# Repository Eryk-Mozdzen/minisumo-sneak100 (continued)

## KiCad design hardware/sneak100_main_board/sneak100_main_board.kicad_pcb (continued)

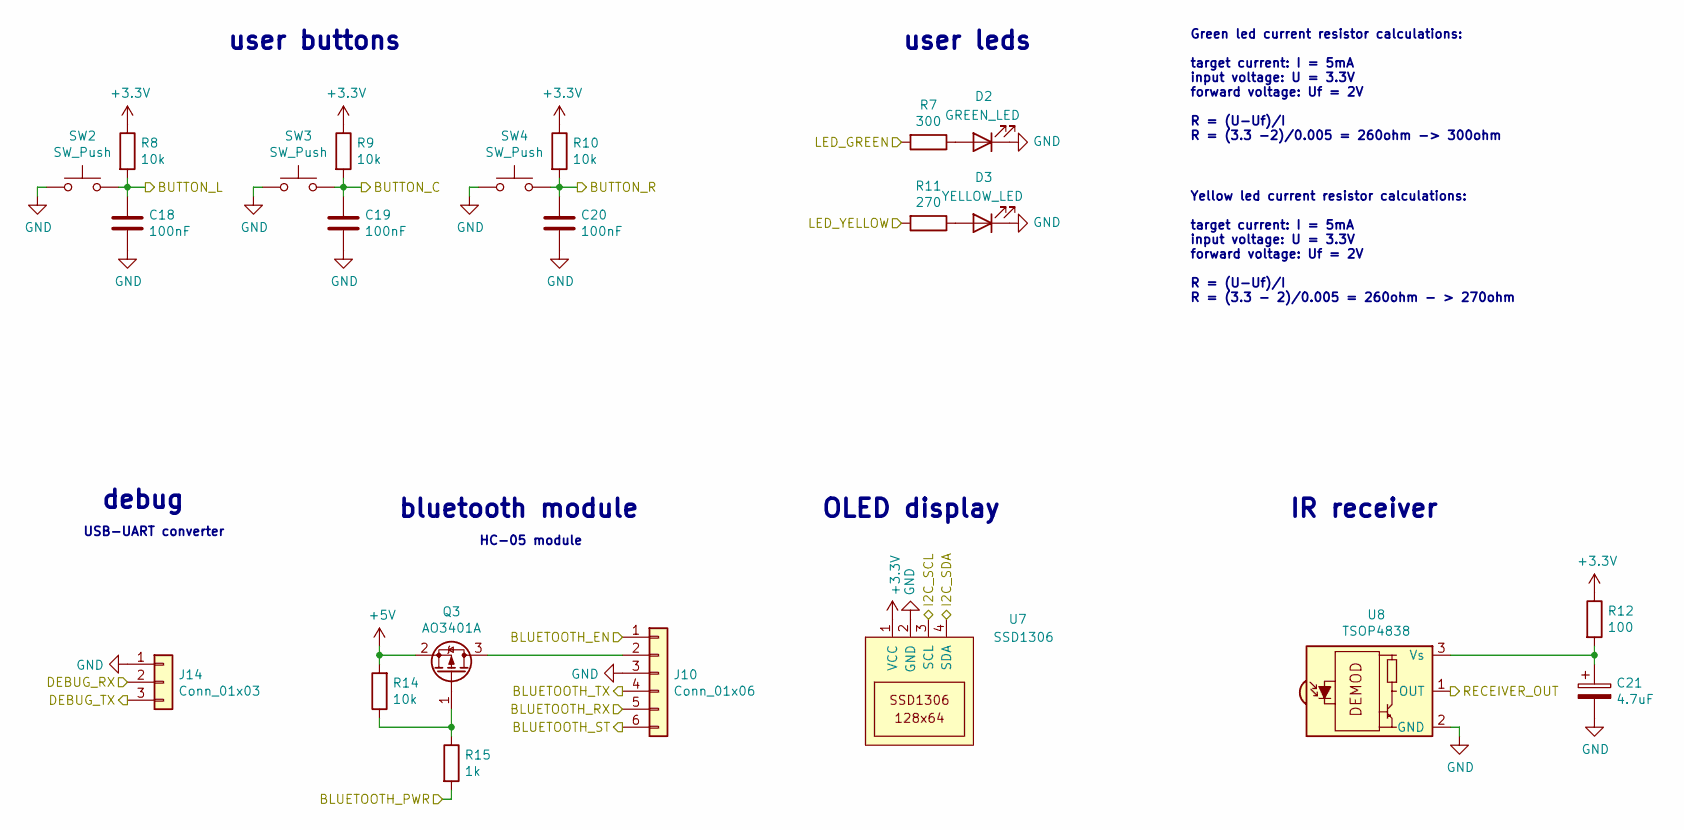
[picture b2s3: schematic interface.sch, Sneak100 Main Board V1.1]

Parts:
C18, C19, C20: 100nF; C_0603_1608Metric
C21: 4.7uF; CP_EIA-3216-18_Kemet-A
D2: GREEN_LED; LED_0603_1608Metric
D3: YELLOW_LED; LED_0603_1608Metric
J10: Conn_01x06; PinSocket_1x06_P2.54mm_Vertical
J14: Conn_01x03; PinSocket_1x03_P2.54mm_Vertical
Q3: AO3401A; SOT-23
R7: 300; R_0603_1608Metric
R8, R9, R10, R14: 10k; R_0603_1608Metric
R11: 270; R_0603_1608Metric
R12: 100; R_0603_1608Metric
R15: 1k; R_0603_1608Metric
SW2, SW3, SW4: SW_Push; SW_Push_1P1T_NO_6x6mm_H9.5mm
U7: SSD1306; SSD1306_module_screw
U8: TSOP4838; PinHeader_1x03_P2.54mm_Vertical

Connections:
+3V3: R8.1, R9.1, R10.1, R12.1, U7.1 (VCC); also elsewhere on the board
+5V: Q3.2 (S), R14.2; also elsewhere on the board
/controller/BLUETOOTH_EN: J10.1; also elsewhere on the board
/controller/BLUETOOTH_PWR: R15.2; also elsewhere on the board
/controller/BLUETOOTH_ST: J10.6; also elsewhere on the board
/controller/I2C1_SCL: U7.3 (SCL); also elsewhere on the board
/controller/I2C1_SDA: U7.4 (SDA); also elsewhere on the board
/controller/RECEIVER_OUT: U8.1 (OUT); also elsewhere on the board
/interface/BLUETOOTH_RX: J10.5; also elsewhere on the board
/interface/BLUETOOTH_TX: J10.4; also elsewhere on the board
/interface/BUTTON_C: C19.1, R9.2, SW3.2; also elsewhere on the board
/interface/BUTTON_L: C18.1, R8.2, SW2.2; also elsewhere on the board
/interface/BUTTON_R: C20.1, R10.2, SW4.2; also elsewhere on the board
/interface/DEBUG_RX: J14.2; also elsewhere on the board
/interface/DEBUG_TX: J14.3; also elsewhere on the board
/interface/LED_GREEN: R7.2; also elsewhere on the board
/interface/LED_YELLOW: R11.2; also elsewhere on the board
GND: C18.2, C19.2, C20.2, C21.2, D2.1 (K), D3.1 (K), J10.3, J14.1, SW2.1, SW3.1, SW4.1, U7.2 (GND), U8.2 (GND); also elsewhere on the board
unnamed: C21.1, R12.2, U8.3 (Vs)
unnamed: D2.2 (A), R7.1
unnamed: D3.2 (A), R11.1
unnamed: J10.2, Q3.3 (D)
unnamed: Q3.1 (G), R14.1, R15.1

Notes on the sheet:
Green led current resistor calculations: target current: I = 5mA input voltage: U = 3.3V forward voltage: Uf = 2V R = (U-Uf)/I R = (3.3 -2)/0.005 = 260ohm -> 300ohm
user buttons
user leds
bluetooth module
OLED display
IR receiver
Yellow led current resistor calculations: target current: I = 5mA input voltage: U = 3.3V forward voltage: Uf = 2V R = (U-Uf)/I R = (3.3 - 2)/0.005 = 260ohm - > 270ohm
HC-05 module
debug
USB-UART converter

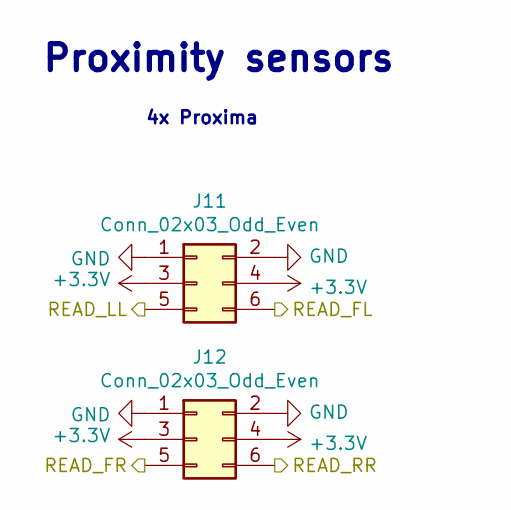
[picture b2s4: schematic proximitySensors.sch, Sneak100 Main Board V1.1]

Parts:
J11, J12: Conn_02x03_Odd_Even; PinSocket_2x03_P2.54mm_Horizontal

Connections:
+3V3: J11.3, J11.4, J12.3, J12.4; also elsewhere on the board
/controller/PROXIMITY_FL: J11.6; also elsewhere on the board
/controller/PROXIMITY_FR: J12.5; also elsewhere on the board
/controller/PROXIMITY_LL: J11.5; also elsewhere on the board
/controller/PROXIMITY_RR: J12.6; also elsewhere on the board
GND: J11.1, J11.2, J12.1, J12.2; also elsewhere on the board

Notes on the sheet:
Proximity sensors
4x Proxima

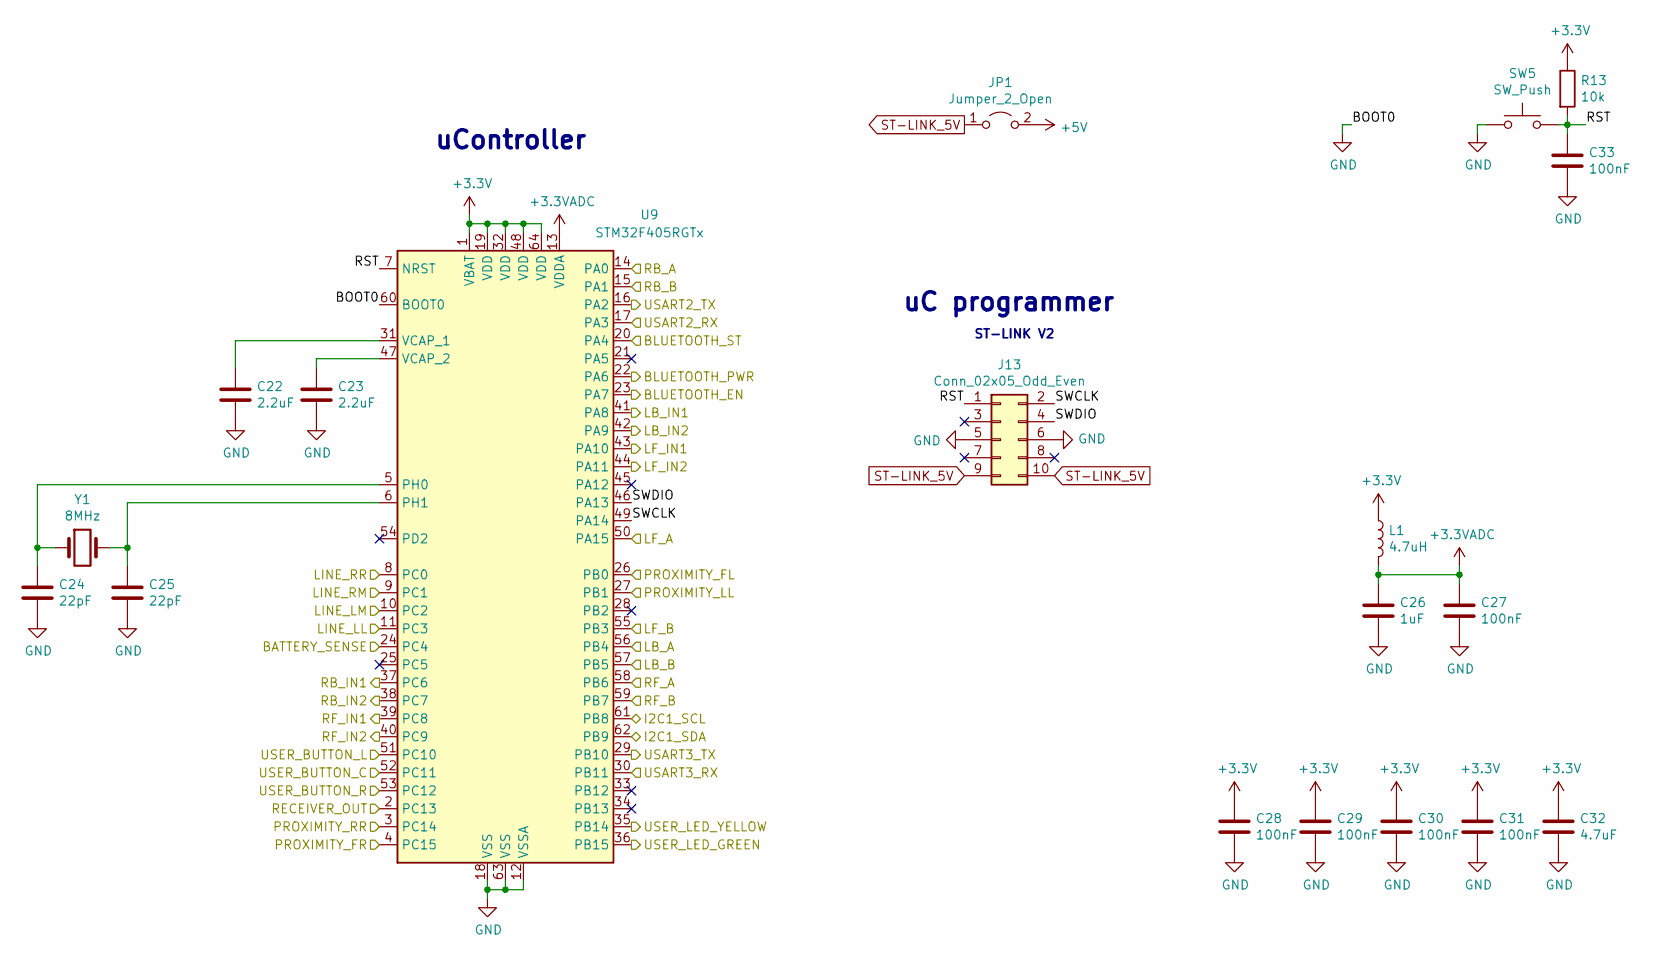
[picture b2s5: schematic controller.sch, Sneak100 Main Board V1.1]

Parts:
C22, C23: 2.2uF; C_0603_1608Metric
C24, C25: 22pF; C_0603_1608Metric
C26: 1uF; C_0603_1608Metric
C27, C28, C29, C30, C31, C33: 100nF; C_0603_1608Metric
C32: 4.7uF; C_0603_1608Metric
J13: Conn_02x05_Odd_Even; IDC-Header_2x05_P2.54mm_Vertical
JP1: Jumper_2_Open; PinHeader_1x03_P2.54mm_Vertical
L1: 4.7uH; L_0805_2012Metric
R13: 10k; R_0603_1608Metric
SW5: SW_Push; SW_Push_1P1T_NO_6x6mm_H9.5mm
U9: STM32F405RGTx; LQFP-64_10x10mm_P0.5mm
Y1: 8MHz; Crystal_SMD_5032-2Pin_5.0x3.2mm

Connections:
+3.3VADC: C26.1, C27.1, L1.2, U9.13 (VDDA)
+3V3: C28.1, C29.1, C30.1, C31.1, C32.1, L1.1, R13.1, U9.1 (VBAT), U9.19 (VDD), U9.32 (VDD), U9.48 (VDD), U9.64 (VDD); also elsewhere on the board
+5V: JP1.2 (B); also elsewhere on the board
/controller/BATTERY_SENSE: U9.24 (PC4); also elsewhere on the board
/controller/BLUETOOTH_EN: U9.23 (PA7); also elsewhere on the board
/controller/BLUETOOTH_PWR: U9.22 (PA6); also elsewhere on the board
/controller/BLUETOOTH_ST: U9.20 (PA4); also elsewhere on the board
/controller/I2C1_SCL: U9.61 (PB8); also elsewhere on the board
/controller/I2C1_SDA: U9.62 (PB9); also elsewhere on the board
/controller/LB_A: U9.56 (PB4); also elsewhere on the board
/controller/LB_B: U9.57 (PB5); also elsewhere on the board
/controller/LB_IN1: U9.41 (PA8); also elsewhere on the board
/controller/LB_IN2: U9.42 (PA9); also elsewhere on the board
/controller/LF_A: U9.50 (PA15); also elsewhere on the board
/controller/LF_B: U9.55 (PB3); also elsewhere on the board
/controller/LF_IN1: U9.43 (PA10); also elsewhere on the board
/controller/LF_IN2: U9.44 (PA11); also elsewhere on the board
/controller/LINE_LL: U9.11 (PC3); also elsewhere on the board
/controller/LINE_LM: U9.10 (PC2); also elsewhere on the board
/controller/LINE_RM: U9.9 (PC1); also elsewhere on the board
/controller/LINE_RR: U9.8 (PC0); also elsewhere on the board
/controller/PROXIMITY_FL: U9.26 (PB0); also elsewhere on the board
/controller/PROXIMITY_FR: U9.4 (PC15); also elsewhere on the board
/controller/PROXIMITY_LL: U9.27 (PB1); also elsewhere on the board
/controller/PROXIMITY_RR: U9.3 (PC14); also elsewhere on the board
/controller/RB_A: U9.14 (PA0); also elsewhere on the board
/controller/RB_B: U9.15 (PA1); also elsewhere on the board
/controller/RB_IN1: U9.37 (PC6); also elsewhere on the board
/controller/RB_IN2: U9.38 (PC7); also elsewhere on the board
/controller/RECEIVER_OUT: U9.2 (PC13); also elsewhere on the board
/controller/RF_A: U9.58 (PB6); also elsewhere on the board
/controller/RF_B: U9.59 (PB7); also elsewhere on the board
/controller/RF_IN1: U9.39 (PC8); also elsewhere on the board
/controller/RF_IN2: U9.40 (PC9); also elsewhere on the board
/controller/RST: C33.1, J13.1, R13.2, SW5.2, U9.7 (NRST)
/controller/SWCLK: J13.2, U9.49 (PA14)
/controller/SWDIO: J13.4, U9.46 (PA13)
/interface/BLUETOOTH_RX: U9.16 (PA2); also elsewhere on the board
/interface/BLUETOOTH_TX: U9.17 (PA3); also elsewhere on the board
/interface/BUTTON_C: U9.52 (PC11); also elsewhere on the board
/interface/BUTTON_L: U9.51 (PC10); also elsewhere on the board
/interface/BUTTON_R: U9.53 (PC12); also elsewhere on the board
/interface/DEBUG_RX: U9.30 (PB11); also elsewhere on the board
/interface/DEBUG_TX: U9.29 (PB10); also elsewhere on the board
/interface/LED_GREEN: U9.36 (PB15); also elsewhere on the board
/interface/LED_YELLOW: U9.35 (PB14); also elsewhere on the board
GND: C22.2, C23.2, C24.2, C25.2, C26.2, C27.2, C28.2, C29.2, C30.2, C31.2, C32.2, C33.2, J13.5, J13.6, SW5.1, U9.12 (VSSA), U9.18 (VSS), U9.60 (BOOT0), U9.63 (VSS); also elsewhere on the board
unnamed: C22.1, U9.31 (VCAP_1)
unnamed: C23.1, U9.47 (VCAP_2)
unnamed: C24.1, U9.5 (PH0), Y1.1
unnamed: C25.1, U9.6 (PH1), Y1.2
ST-LINK_5V: J13.9, J13.10, JP1.1 (A)

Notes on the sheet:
uController
uC programmer
ST-LINK V2

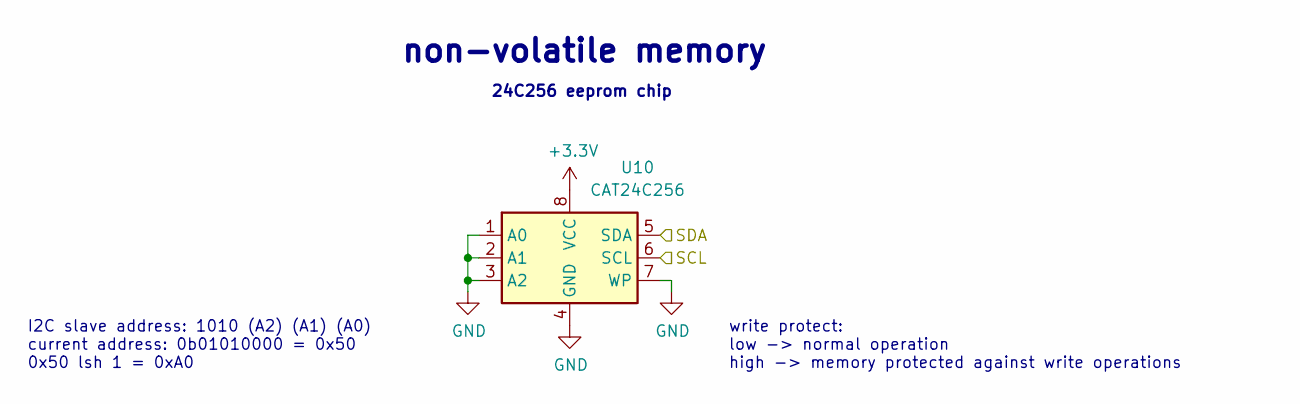
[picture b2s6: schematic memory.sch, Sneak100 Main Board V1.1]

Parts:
U10: CAT24C256; SOIC-8_3.9x4.9mm_P1.27mm

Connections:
+3V3: U10.8 (VCC); also elsewhere on the board
/controller/I2C1_SCL: U10.6 (SCL); also elsewhere on the board
/controller/I2C1_SDA: U10.5 (SDA); also elsewhere on the board
GND: U10.1 (A0), U10.2 (A1), U10.3 (A2), U10.4 (GND), U10.7 (WP); also elsewhere on the board

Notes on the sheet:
I2C slave address: 1010 (A2) (A1) (A0) current address: 0b01010000 = 0x50 0x50 lsh 1 = 0xA0
write protect: low -> normal operation high -> memory protected against write operations
non-volatile memory
24C256 eeprom chip

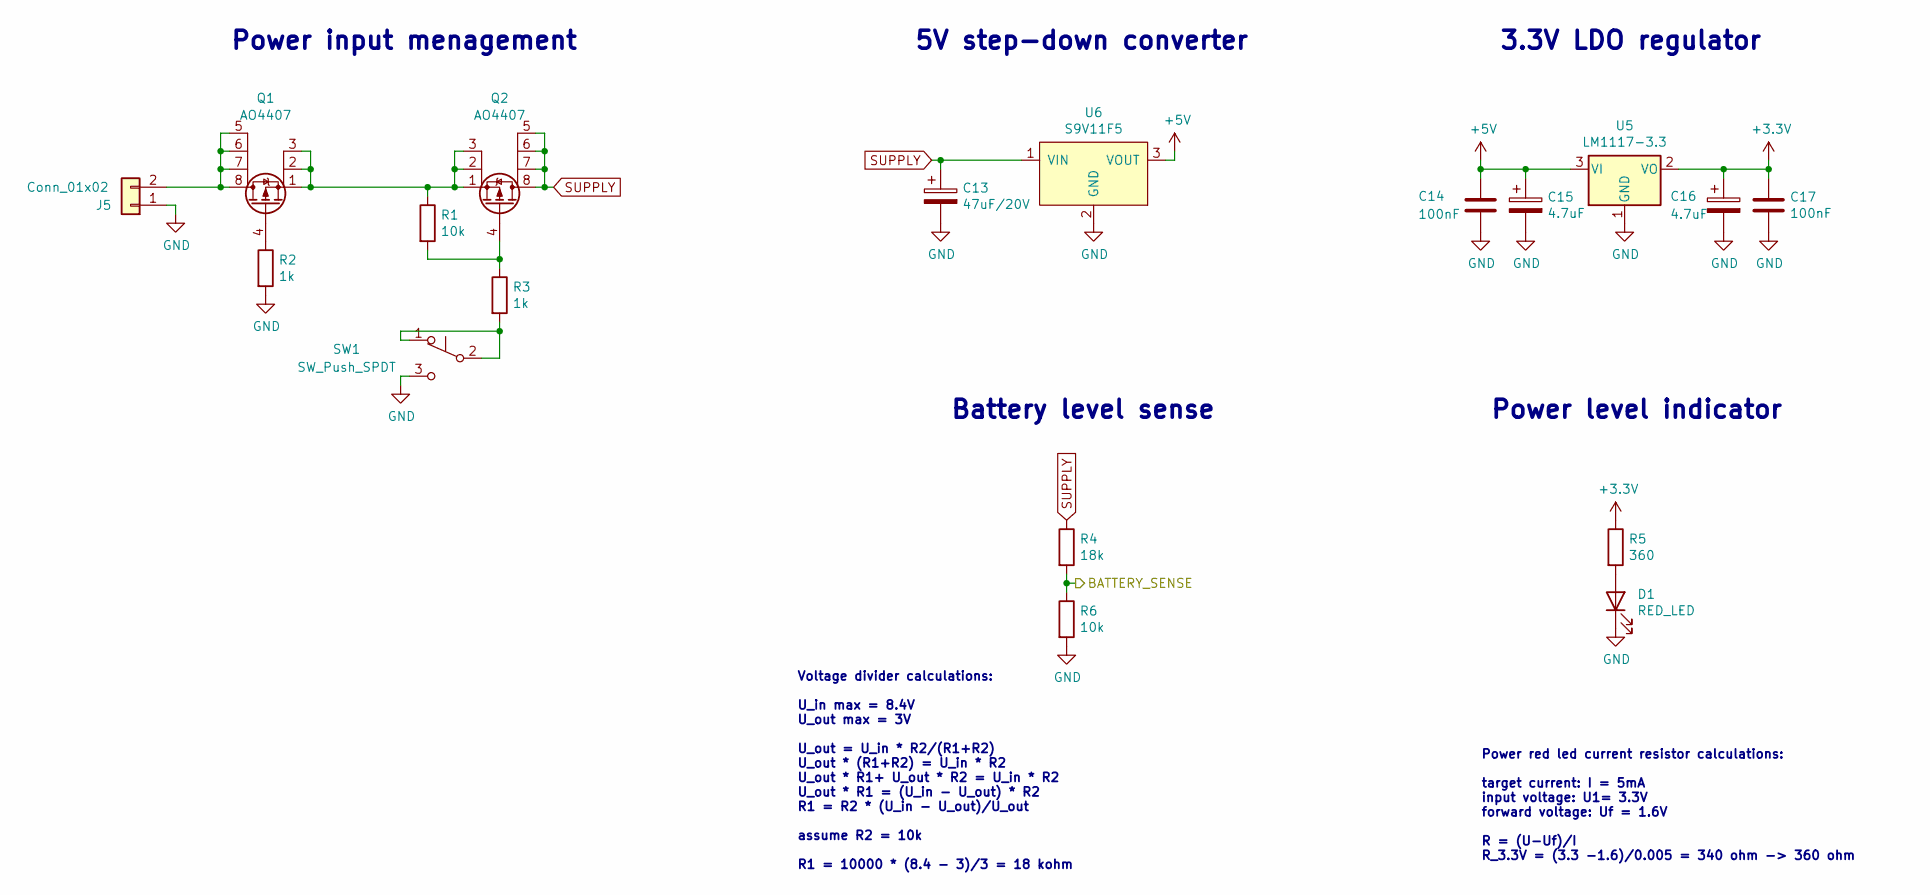
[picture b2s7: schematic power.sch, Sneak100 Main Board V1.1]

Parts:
C13: 47uF/20V; CP_EIA-7343-31_Kemet-D
C14, C17: 100nF; C_0603_1608Metric
C15, C16: 4.7uF; CP_EIA-3216-18_Kemet-A
D1: RED_LED; LED_0603_1608Metric
J5: Conn_01x02; PinHeader_1x02_P2.54mm_Horizontal
Q1, Q2: AO4407; SOIC-8_3.9x4.9mm_P1.27mm
R1, R6: 10k; R_0603_1608Metric
R2, R3: 1k; R_0603_1608Metric
R4: 18k; R_0603_1608Metric
R5: 360; R_0603_1608Metric
SW1: SW_Push_SPDT; ESP2010_90
U5: LM1117-3.3; SOT-223-3_TabPin2
U6: S9V11F5; S9V11F5_module

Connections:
+3V3: C16.1, C17.1, R5.1, U5.2 (VO); also elsewhere on the board
+5V: C14.1, C15.1, U5.3 (VI), U6.3 (VOUT); also elsewhere on the board
/controller/BATTERY_SENSE: R4.2, R6.1; also elsewhere on the board
GND: C13.2, C14.2, C15.2, C16.2, C17.2, D1.1 (K), J5.1, R2.2, R6.2, SW1.3 (C), U5.1 (GND), U6.2 (GND); also elsewhere on the board
unnamed: D1.2 (A), R5.2
unnamed: J5.2, Q1.5, Q1.6, Q1.7, Q1.8
unnamed: Q1.1, Q1.2, Q1.3, Q2.1, Q2.2, Q2.3, R1.1
unnamed: Q1.4, R2.1
unnamed: Q2.4, R1.2, R3.1
unnamed: R3.2, SW1.1 (A), SW1.2 (B)
SUPPLY: C13.1, Q2.5, Q2.6, Q2.7, Q2.8, R4.1, U6.1 (VIN); also elsewhere on the board

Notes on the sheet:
5V step-down converter
Battery level sense
Power level indicator
Power input menagement
3.3V LDO regulator
Voltage divider calculations: U_in max = 8.4V U_out max = 3V U_out = U_in * R2/(R1+R2) U_out * (R1+R2) = U_in * R2 U_out * R1+ U_out * R2 = U_in * R2 U_out * R1 = (U_in - U_out) * R2 R1 = R2 * (U_in - U_out)/U_out assume R2 = 10k R1 = 10000 * (8.4 - 3)/3 = 18 kohm
Power red led current resistor calculations: target current: I = 5mA input voltage: U1= 3.3V forward voltage: Uf = 1.6V R = (U-Uf)/I R_3.3V = (3.3 -1.6)/0.005 = 340 ohm -> 360 ohm

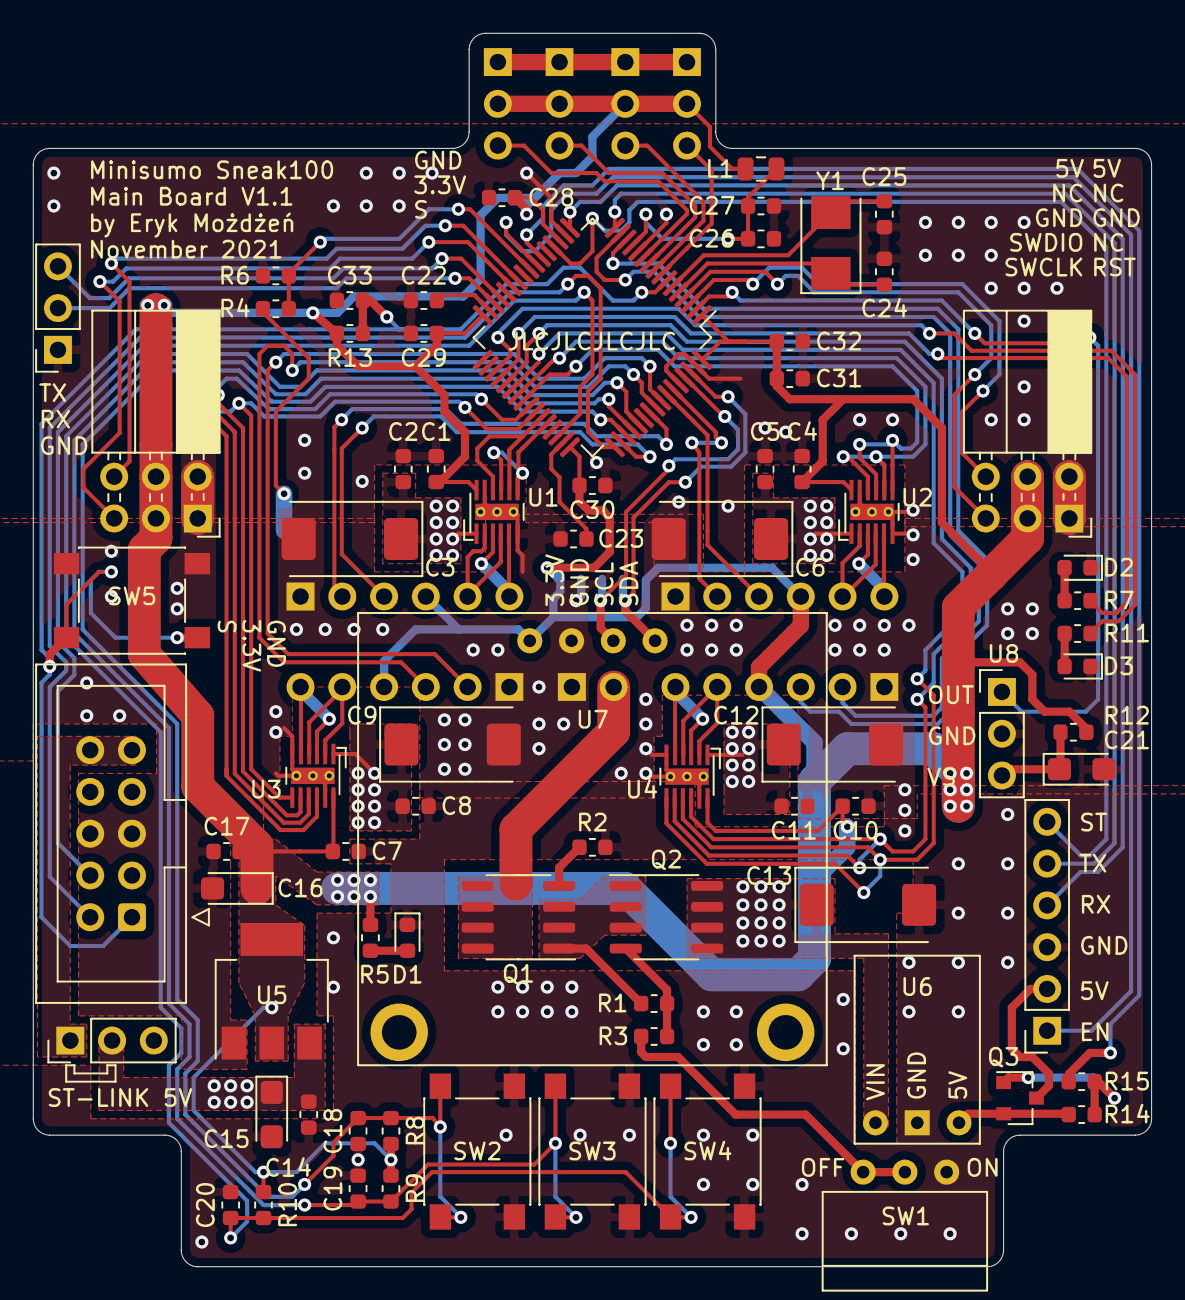
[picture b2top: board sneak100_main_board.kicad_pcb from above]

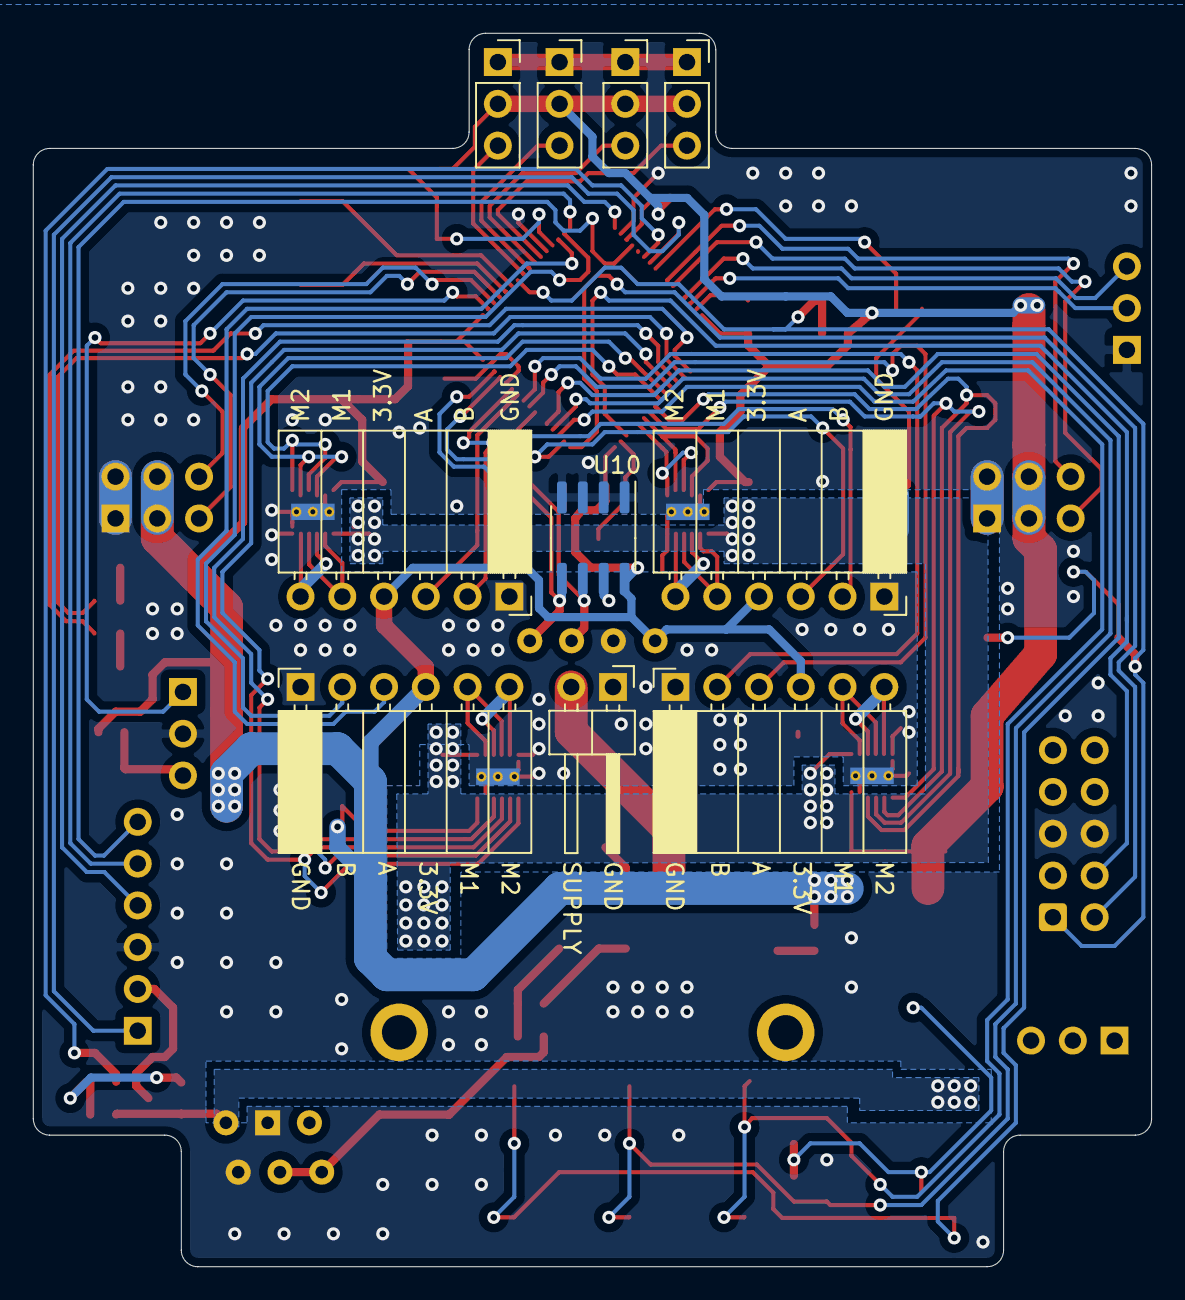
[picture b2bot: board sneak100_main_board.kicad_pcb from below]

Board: 2 copper layers, 68.0 x 75.0 mm, 86 parts (10 on the bottom side), 72 nets.

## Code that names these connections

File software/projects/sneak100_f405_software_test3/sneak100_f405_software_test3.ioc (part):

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Mcu.Name=STM32F405RGTx
Mcu.Package=LQFP64
Mcu.UserName=STM32F405RGTx
PA0-WKUP.GPIOParameters=GPIO_Label
PA0-WKUP.GPIO_Label=MOT1_IN1
PA0-WKUP.Signal=S_TIM5_CH1
PA1.GPIOParameters=GPIO_Label
PA1.GPIO_Label=MOT1_IN2
PA1.Signal=S_TIM5_CH2
PA11.GPIOParameters=GPIO_Label
PA11.GPIO_Label=USB_DM
PA11.Mode=Device_Only
PA11.Signal=USB_OTG_FS_DM
PA12.GPIOParameters=GPIO_Label
PA12.GPIO_Label=USB_DP
PA12.Mode=Device_Only
PA12.Signal=USB_OTG_FS_DP
PA13.Mode=Serial_Wire
PA13.Signal=SYS_JTMS-SWDIO
PA14.Mode=Serial_Wire
PA14.Signal=SYS_JTCK-SWCLK
PA15.GPIOParameters=GPIO_Label
PA15.GPIO_Label=MOT4_IN1
PA15.Signal=S_TIM2_CH1_ETR
PA2.GPIOParameters=GPIO_Label
PA2.GPIO_Label=MOT2_IN1
PA2.Signal=S_TIM5_CH3
PA3.GPIOParameters=GPIO_Label
PA3.GPIO_Label=MOT2_IN2
PA3.Signal=S_TIM5_CH4
PA4.GPIOParameters=GPIO_Label
PA4.GPIO_Label=PROX2
PA4.Signal=GPIO_Input
PA5.GPIOParameters=GPIO_Label
PA5.GPIO_Label=PROX1
PA5.Signal=GPIO_Input
PA6.GPIOParameters=GPIO_Label
PA6.GPIO_Label=LED_G
PA6.Signal=GPIO_Output
PA7.GPIOParameters=GPIO_Label
PA7.GPIO_Label=PROX_GEN
PA7.Signal=S_TIM14_CH1
PA8.GPIOParameters=GPIO_Label
PA8.GPIO_Label=MOT2_A
PA8.Signal=S_TIM1_CH1
PA9.GPIOParameters=GPIO_Label
PA9.GPIO_Label=MOT2_B
PA9.Signal=S_TIM1_CH2
PB0.GPIOParameters=GPIO_Label
PB0.GPIO_Label=SW3
PB0.Signal=GPIO_Input
PB1.GPIOParameters=GPIO_Label
PB1.GPIO_Label=SW2
PB1.Signal=GPIO_Input
PB10.GPIOParameters=GPIO_Label
PB10.GPIO_Label=MOT3_IN1
PB10.Signal=S_TIM2_CH3
PB11.GPIOParameters=GPIO_Label
PB11.GPIO_Label=MOT3_IN2
PB11.Signal=S_TIM2_CH4
PB12.GPIOParameters=GPIO_Label
PB12.GPIO_Label=BUTT1
PB12.Signal=GPIO_Input
PB13.GPIOParameters=GPIO_Label
PB13.GPIO_Label=BUTT2
PB13.Signal=GPIO_Input
PB14.GPIOParameters=GPIO_Label
PB14.GPIO_Label=BUTT3
PB14.Signal=GPIO_Input
PB2.GPIOParameters=GPIO_Label
PB2.GPIO_Label=SW1
PB2.Signal=GPIO_Input
PB3.GPIOParameters=GPIO_Label
PB3.GPIO_Label=MOT4_IN2
PB3.Signal=S_TIM2_CH2
PB4.GPIOParameters=GPIO_Label
PB4.GPIO_Label=MOT3_A
PB4.Signal=S_TIM3_CH1
PB5.GPIOParameters=GPIO_Label
PB5.GPIO_Label=MOT3_B
PB5.Signal=S_TIM3_CH2
PB6.GPIOParameters=GPIO_Label
PB6.GPIO_Label=MOT4_A
PB6.Signal=S_TIM4_CH1
PB7.GPIOParameters=GPIO_Label
PB7.GPIO_Label=MOT4_B
PB7.Signal=S_TIM4_CH2
PB8.GPIOParameters=GPIO_Label
PB8.GPIO_Label=SCL
PB8.Mode=I2C
PB8.Signal=I2C1_SCL
PB9.GPIOParameters=GPIO_Label
PB9.GPIO_Label=SDA
PB9.Mode=I2C
PB9.Signal=I2C1_SDA
PC0.GPIOParameters=GPIO_Label
PC0.GPIO_Label=LINE1
PC0.Signal=ADCx_IN10
PC1.GPIOParameters=GPIO_Label
PC1.GPIO_Label=LINE2
PC1.Signal=ADCx_IN11
PC10.GPIOParameters=GPIO_Label
PC10.GPIO_Label=MTX
PC10.Mode=Asynchronous
PC10.Signal=UART4_TX
PC11.GPIOParameters=GPIO_Label
PC11.GPIO_Label=MRX
PC11.Mode=Asynchronous
PC11.Signal=UART4_RX
PC12.GPIOParameters=GPIO_Label
PC12.GPIO_Label=LED_Y
PC12.Signal=GPIO_Output
PC13-ANTI_TAMP.GPIOParameters=GPIO_Label
PC13-ANTI_TAMP.GPIO_Label=PROX4
PC13-ANTI_TAMP.Signal=GPIO_Input
PC14-OSC32_IN.GPIOParameters=GPIO_Label
PC14-OSC32_IN.GPIO_Label=PROX3
PC14-OSC32_IN.Signal=GPIO_Input
PC15-OSC32_OUT.GPIOParameters=GPIO_Label
PC15-OSC32_OUT.GPIO_Label=RECIV
PC15-OSC32_OUT.Signal=GPXTI15
PC2.GPIOParameters=GPIO_Label
PC2.GPIO_Label=LINE3
PC2.Signal=ADCx_IN12
PC3.GPIOParameters=GPIO_Label
PC3.GPIO_Label=LINE4
PC3.Signal=ADCx_IN13
PC4.GPIOParameters=GPIO_Label
PC4.GPIO_Label=BATTERY
PC4.Signal=ADCx_IN14
PC6.GPIOParameters=GPIO_Label
PC6.GPIO_Label=MOT1_A
PC6.Signal=S_TIM8_CH1
PC7.GPIOParameters=GPIO_Label
PC7.GPIO_Label=MOT1_B
PC7.Signal=S_TIM8_CH2
PH0-OSC_IN.Mode=HSE-External-Oscillator
PH0-OSC_IN.Signal=RCC_OSC_IN
PH1-OSC_OUT.Mode=HSE-External-Oscillator
PH1-OSC_OUT.Signal=RCC_OSC_OUT
RCC.HSE_VALUE=8000000
RCC.SYSCLKFreq_VALUE=168000000
RCC.SYSCLKSource=RCC_SYSCLKSOURCE_PLLCLK
board=custom

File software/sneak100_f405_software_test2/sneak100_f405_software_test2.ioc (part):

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Mcu.Name=STM32F405RGTx
Mcu.Package=LQFP64
Mcu.UserName=STM32F405RGTx
PA0-WKUP.GPIOParameters=GPIO_Label
PA0-WKUP.GPIO_Label=MOTOR_RB_A
PA0-WKUP.Signal=S_TIM5_CH1
PA1.GPIOParameters=GPIO_Label
PA1.GPIO_Label=MOTOR_RB_B
PA1.Signal=S_TIM5_CH2
PA10.GPIOParameters=GPIO_Label
PA10.GPIO_Label=MOTOR_LF_IN1
PA10.Signal=S_TIM1_CH3
PA11.GPIOParameters=GPIO_Label
PA11.GPIO_Label=MOTOR_LF_IN2
PA11.Signal=S_TIM1_CH4
PA13.Mode=Serial_Wire
PA13.Signal=SYS_JTMS-SWDIO
PA14.Mode=Serial_Wire
PA14.Signal=SYS_JTCK-SWCLK
PA15.GPIOParameters=GPIO_Label
PA15.GPIO_Label=MOTOR_LF_A
PA15.Signal=S_TIM2_CH1_ETR
PA2.Mode=Asynchronous
PA2.Signal=USART2_TX
PA3.Mode=Asynchronous
PA3.Signal=USART2_RX
PA4.GPIOParameters=GPIO_Label
PA4.GPIO_Label=BLUETOOTH_ST
PA4.Signal=GPIO_Input
PA6.GPIOParameters=GPIO_Label,GPIO_ModeDefaultOutputPP
PA6.GPIO_Label=BLUETOOTH_PWR
PA6.GPIO_ModeDefaultOutputPP=GPIO_MODE_OUTPUT_OD
PA6.Signal=GPIO_Output
PA7.GPIOParameters=GPIO_Label
PA7.GPIO_Label=BLUETOOTH_EN
PA7.Signal=GPIO_Input
PA8.GPIOParameters=GPIO_Label
PA8.GPIO_Label=MOTOR_LB_IN1
PA8.Signal=S_TIM1_CH1
PA9.GPIOParameters=GPIO_Label
PA9.GPIO_Label=MOTOR_LB_IN2
PA9.Signal=S_TIM1_CH2
PB0.GPIOParameters=GPIO_Label
PB0.GPIO_Label=PROXIMITY_FL
PB0.Signal=GPIO_Input
PB1.GPIOParameters=GPIO_Label
PB1.GPIO_Label=PROXIMITY_LL
PB1.Signal=GPIO_Input
PB10.Mode=Asynchronous
PB10.Signal=USART3_TX
PB11.Mode=Asynchronous
PB11.Signal=USART3_RX
PB14.GPIOParameters=GPIO_Label
PB14.GPIO_Label=USER_LED_YELLOW
PB14.Signal=GPIO_Output
PB15.GPIOParameters=GPIO_Label
PB15.GPIO_Label=USER_LED_GREEN
PB15.Signal=GPIO_Output
PB3.GPIOParameters=GPIO_Label
PB3.GPIO_Label=MOTOR_LF_B
PB3.Signal=S_TIM2_CH2
PB4.GPIOParameters=GPIO_Label
PB4.GPIO_Label=MOTOR_LB_A
PB4.Signal=S_TIM3_CH1
PB5.GPIOParameters=GPIO_Label
PB5.GPIO_Label=MOTOR_LB_B
PB5.Signal=S_TIM3_CH2
PB6.GPIOParameters=GPIO_Label
PB6.GPIO_Label=MOTOR_RF_A
PB6.Signal=S_TIM4_CH1
PB7.GPIOParameters=GPIO_Label
PB7.GPIO_Label=MOTOR_RF_B
PB7.Signal=S_TIM4_CH2
PB8.Mode=I2C
PB8.Signal=I2C1_SCL
PB9.Mode=I2C
PB9.Signal=I2C1_SDA
PC0.GPIOParameters=GPIO_Label
PC0.GPIO_Label=LINE_RR
PC0.Signal=ADCx_IN10
PC1.GPIOParameters=GPIO_Label
PC1.GPIO_Label=LINE_RM
PC1.Signal=ADCx_IN11
PC10.GPIOParameters=GPIO_Label
PC10.GPIO_Label=USER_BUTTON_L
PC10.Signal=GPIO_Input
PC11.GPIOParameters=GPIO_Label
PC11.GPIO_Label=USER_BUTTON_C
PC11.Signal=GPIO_Input
PC12.GPIOParameters=GPIO_Label
PC12.GPIO_Label=USER_BUTTON_R
PC12.Signal=GPIO_Input
PC13-ANTI_TAMP.GPIOParameters=GPIO_Label
PC13-ANTI_TAMP.GPIO_Label=RECEIVER_OUT
PC13-ANTI_TAMP.Signal=GPXTI13
PC14-OSC32_IN.GPIOParameters=GPIO_Label
PC14-OSC32_IN.GPIO_Label=PROXIMITY_RR
PC14-OSC32_IN.Signal=GPIO_Input
PC15-OSC32_OUT.GPIOParameters=GPIO_Label
PC15-OSC32_OUT.GPIO_Label=PROXIMITY_FR
PC15-OSC32_OUT.Signal=GPIO_Input
PC2.GPIOParameters=GPIO_Label
PC2.GPIO_Label=LINE_LM
PC2.Signal=ADCx_IN12
PC3.GPIOParameters=GPIO_Label
PC3.GPIO_Label=LINE_LL
PC3.Signal=ADCx_IN13
PC4.GPIOParameters=GPIO_Label
PC4.GPIO_Label=BATTERY_SENSE
PC4.Signal=ADCx_IN14
PC6.GPIOParameters=GPIO_Label
PC6.GPIO_Label=MOTOR_RB_IN1
PC6.Signal=S_TIM8_CH1
PC7.GPIOParameters=GPIO_Label
PC7.GPIO_Label=MOTOR_RB_IN2
PC7.Signal=S_TIM8_CH2
PC8.GPIOParameters=GPIO_Label
PC8.GPIO_Label=MOTOR_RF_IN1
PC8.Signal=S_TIM8_CH3
PC9.GPIOParameters=GPIO_Label
PC9.GPIO_Label=MOTOR_RF_IN2
PC9.Signal=S_TIM8_CH4
PH0-OSC_IN.Mode=HSE-External-Oscillator
PH0-OSC_IN.Signal=RCC_OSC_IN
PH1-OSC_OUT.Mode=HSE-External-Oscillator
PH1-OSC_OUT.Signal=RCC_OSC_OUT
RCC.HSE_VALUE=8000000
RCC.SYSCLKFreq_VALUE=168000000
RCC.SYSCLKSource=RCC_SYSCLKSOURCE_PLLCLK
board=custom

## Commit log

2021-05-13 old models
2021-05-14 Hull raw model
2021-05-14 top hull and electronics
2021-06-29 Hull modeling in progress
2021-06-29 Mid hull corrections and phototransistor
2021-06-30 Front sensors and hull bolts
2021-07-01 Line sensors mount
2021-07-01 Wheel dimension fix
2021-07-01 Side sensors
2021-07-02 Side sensors complete
2021-07-02 Blade bolds
2021-07-02 STM32F411 pinout check
2021-07-03 line and proximity sensors schematic
2021-07-03 User buttons, leds and uart
2021-07-04 Gap for motor mount and holes
2021-07-05 Hull small changes
2021-07-05 Generating stl files for 3D printing
2021-07-07 Proximity sensor first test
2021-07-08 motors circuit scheme
2021-07-08 Add stm32f405 uC scheme
2021-07-08 F405 first hardware configuration
2021-07-08 F405 better hardware configuration
2021-07-08 Hardware configuration schematic
2021-07-08 Change usb connector footprint
2021-07-09 Power section scheme
2021-07-14 USB FDU mode
2021-07-15 Layout progress
2021-07-21 Add OLED display
2021-07-23 Board interface layout
2021-07-24 PCB first full layout
2021-07-24 Better photo for README
2021-07-25 More space in top hull and schematic fix
2021-07-26 bluetooth en & status connection
2021-07-26 First routes on PCB
2021-08-02 Add external proximity sensor, erase old from schematic
2021-08-07 Hull with external proximity sensors
2021-08-07 line sensors connectors
2021-08-08 power rails routed
2021-08-08 Motor signals and interface
2021-08-08 Remaining signals from uC
2021-08-09 proximity sensors connectors
2021-08-10 programmer connector, proximity sensors routed
2021-08-10 ground fill zones and vias
2021-08-11 3.3V power lines
2021-08-12 Silk layer text
2021-08-14 Generate gerbers
2021-08-14 Add thermal gap to motor bridges
2021-08-15 pid & time base
2021-08-15 motor bridges solid thermal pad
2021-08-15 component list and values fix
2021-08-16 Bigger tantalum capacitors
2021-08-20 Add split into hardware and abstraction layer
2021-08-21 Motors & encoder software fix
2021-08-22 display external lib
2021-08-22 Display update time reduced
2021-08-27 Bluetooth implementation begin
2021-08-28 Add bluetooth functions
2021-08-28 time base from hal_tick
2021-08-29 Bluetooth config return status
2021-08-29 Bluetooth uart DMA
2021-08-30 Hull smoothing
2021-09-10 Bluetooth software fix
2021-09-10 ADC reading implementation
2021-09-10 Parts list update
2021-09-12 Add bigger gaps
2021-09-12 First 3D prints
2021-09-20 Start creation of documentation
2021-09-25 First documentation
2021-09-28 Version 1.1 begin
2021-09-28 uController routes in progress
2021-09-29 uController routes finish
2021-09-29 Version 1.1 probably finished
2021-09-29 Electric models update
2021-09-29 Hull top upgrades
2021-11-15 gerbers for V1.1 main board
2021-11-17 Add eeprom chip
2021-11-17 Update gerbers
2021-11-17 update date and title of schematic
2021-11-28 Reorganize files
2021-11-28 non-volatile memory code
2021-11-28 Display data
2021-12-12 update workflow
2021-12-23 generate schematic V1.1 and fix uart lines directions
2022-01-24 2nd board test
2022-01-25 clean software repo, add submodule
2022-01-25 More cleaning
2022-01-25 better cleaning
2022-01-26 update list
2022-01-26 begin of GUI implementation
2022-01-26 working cute GUI
2022-01-26 MOTORS WORKS
2022-01-27 code renovation and bug fixes
2022-01-27 add rc5 decoder
2022-01-27 better main menu
2022-02-01 update hardware whislist
2022-02-13 GUI settings and read/write data to EEPROM
2022-02-14 major file management update
2022-02-14 shorter names
2022-02-14 cleaning
2022-02-14 bluetooth testing
2022-02-16 bluetooth funny discovery
2022-02-16 bluetooth fix implementation
2022-02-16 update diagram
2022-02-17 UART DMA buffer for CLI
2022-02-17 begin of Command Line Interface (CLI)
2022-02-17 CLI working
2022-02-17 CLI error to fix
2022-02-18 CLI fix success
2022-02-18 bluetooth CLI fix
2022-02-19 planned CLI commands list
2022-02-19 CLI commands ready
2022-02-19 update readmy and docs
2022-02-20 exception handling and interrupt usage fix
2022-02-20 begin of core FSM
2022-02-21 major progress in core FSM
2022-02-21 GUI cleaning
2022-02-22 add graphical enter to fight FSM
2022-02-22 add button start mode 5 seconds delay
2022-02-22 GUI menu update
2022-02-24 naming unification
2022-02-24 add button struct
2022-02-24 add external display lib
2022-02-24 menu select fix
2022-02-24 include fix
2022-02-26 hull errors fix and test print
2022-02-27 3d models fixes
2022-02-27 more printing
2022-02-28 line sensors new mount
2022-03-01 line sensors mount fix
2022-03-22 wheel velocity close loop control
2022-03-29 add battery low warning
2022-03-29 line sensors ready
2022-04-02 input filtering
2022-04-07 Rybnik speedrun: hull with lead
2022-04-08 Rybnik speedrun: robot have correct mass!
2022-04-08 Rybnik speedrun: simple fight algorithm
2022-04-12 update 3d model
2022-04-23 start RTOS development
2022-04-23 add CLI
2022-04-24 PCB version V2.0 started
2022-04-24 PCB version 2.0 schematic progress
2022-04-26 motor PWM frequency inaudible now
2022-04-26 include BOOT1 switch into new PCB
2022-04-29 small improvements
2022-04-29 footprints and first layout
2022-05-10 fix cables to proximity sensors
2022-07-09 Add photos
2022-07-15 update project template
2022-07-15 motors in close loop
2022-07-15 configuration of second uart
2022-07-16 add proximity sensors
2022-07-16 add battery voltage and temperature
2022-07-16 read eeprom
2022-07-16 screen utils
2022-07-16 flip screen
2022-07-17 draw on screen formatted text and bitmaps
2022-07-19 GUI development
2022-07-19 GUI view panels
2022-07-19 peripheral function fix
2022-07-20 clening and fixing
2022-07-20 line sensors quick fix (hardware need to be fix)
2022-07-21 add more CLI commands
2022-07-22 revert 3d model changes to current one
2022-07-23 read rc5 frames
2022-07-25 robot state machine
2022-07-25 eeprom tested and work
2022-07-25 main state machine ready
2022-07-25 fight state machine
2022-07-26 fight and explore
2022-07-26 constants fixes and edge-robot angle measurement
2022-07-26 exploring and turning work!
2022-07-26 motors dead power region compensation
2022-09-02 raport update
2022-10-08 simplify directory tree
2022-10-30 Bukareszt speedrun: motor fix
2022-11-15 turn on the gui
2022-11-16 add hardware pullups for i2c
2022-11-26 servo code
2023-01-29 add konar to raport
2023-01-29 remove old raport
2023-02-14 update photos
